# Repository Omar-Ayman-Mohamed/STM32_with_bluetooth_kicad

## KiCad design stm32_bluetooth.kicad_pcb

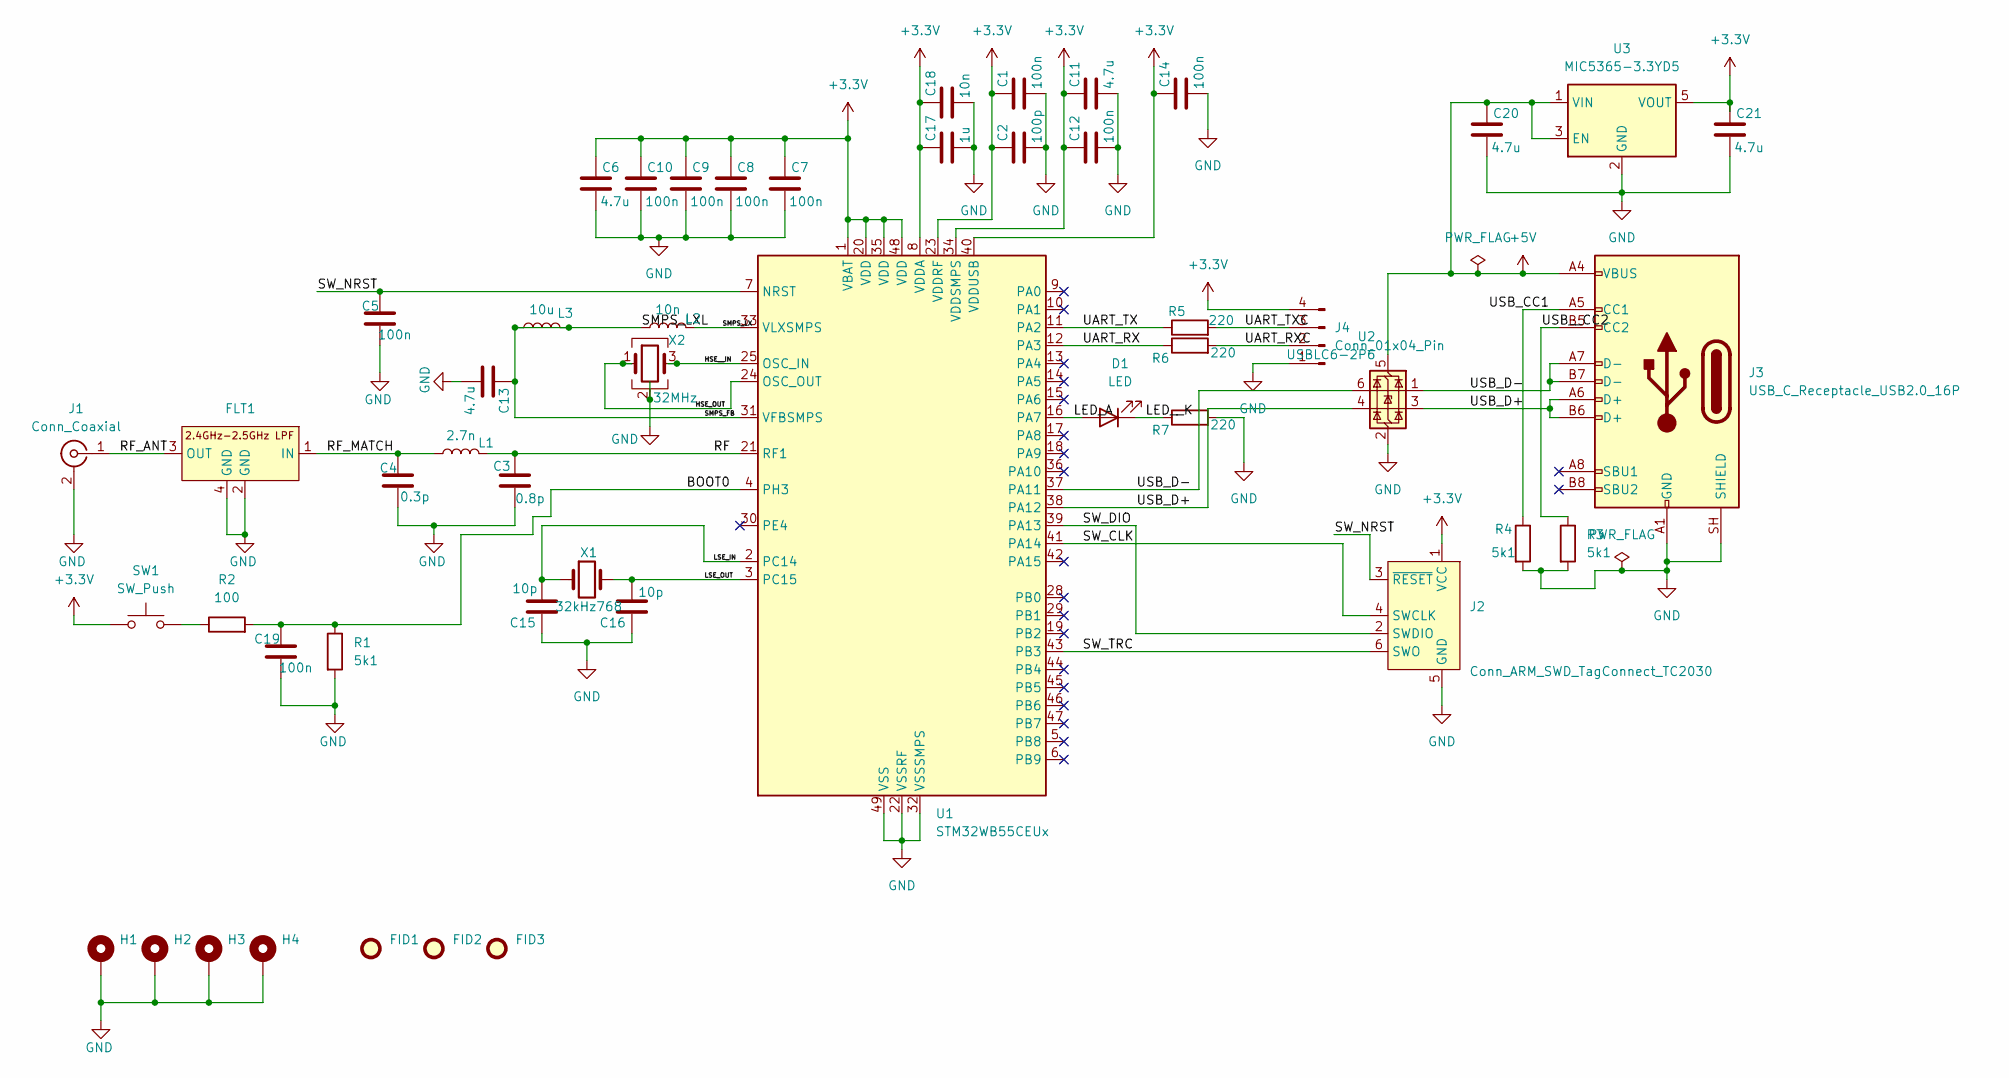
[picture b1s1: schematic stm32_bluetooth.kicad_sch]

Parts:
C1, C5, C7, C8, C9, C10, C12, C14, C19: 100n; C_0402_1005Metric
C2: 100p; C_0603_1608Metric
C3: 0.8p; C_0402_1005Metric
C4: 0.3p; C_0402_1005Metric
C6, C11, C13, C20, C21: 4.7u; C_0603_1608Metric
C15, C16: 10p; C_0402_1005Metric
C17: 1u; C_0603_1608Metric
C18: 10n; C_0402_1005Metric
D1: LED; LED_0402_1005Metric
FID1, FID2, FID3: Fiducial; Fiducial_1mm_Mask2mm
FLT1: DLF162500LT-5028A1
H1, H2, H3, H4: MountingHole_Pad; MountingHole_2.2mm_M2_Pad_Via
J1: Conn_Coaxial; U.FL_Hirose_U.FL-R-SMT-1_Vertical
J2: Conn_ARM_SWD_TagConnect_TC2030; Tag-Connect_TC2030-IDC-FP_2x03_P1.27mm_Vertical
J3: USB_C_Receptacle_USB2.0_16P; USB_C_Receptacle_GCT_USB4105-xx-A_16P_TopMnt_Horizontal
J4: Conn_01x04_Pin; Molex_PicoBlade_53048-0410_1x04_P1.25mm_Horizontal
L1: 2.7n; L_0402_1005Metric
L2: 10n; L_0402_1005Metric
L3: 10u; L_0805_2012Metric
R1, R3, R4: 5k1; R_0402_1005Metric
R2: 100; R_0402_1005Metric
R5, R6, R7: 220; R_0402_1005Metric
SW1: SW_Push; SW_SPST_CK_RS282G05A3
U1: STM32WB55CEUx; QFN-48-1EP_7x7mm_P0.5mm_EP5.6x5.6mm
U2: USBLC6-2P6; SOT-666
U3: MIC5365-3.3YD5; TSOT-23-5
X1: 32kHz768; Crystal_SMD_2012-2Pin_2.0x1.2mm
X2: 32MHz; Crystal_SMD_2016-4Pin_2.0x1.6mm

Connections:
+3.3V: C1.1, C2.1, C6.1, C7.1, C8.1, C9.1, C10.1, C11.1, C12.1, C14.1, C17.1, C18.1, C21.1, J2.1 (VCC), J4.4, SW1.1, U1.1 (VBAT), U1.8 (VDDA), U1.20 (VDD), U1.23 (VDDRF), U1.34 (VDDSMPS), U1.35 (VDD), U1.40 (VDDUSB), U1.48 (VDD), U3.5 (VOUT)
+5V: C20.1, J3.A4 (VBUS), J3.A9 (VBUS), J3.B4 (VBUS), J3.B9 (VBUS), U2.5 (VBUS), U3.1 (VIN), U3.3 (EN)
/BOOT0: C19.2, R1.1, R2.2, U1.4 (PH3)
/HSE_OUT: U1.24 (OSC_OUT), X2.1
/HSE__IN: U1.25 (OSC_IN), X2.3
/LED_A: D1.2 (A), U1.16 (PA7)
/LED__K: D1.1 (K), R7.1
/LSE_IN: C15.2, U1.2 (PC14), X1.1
/LSE_OUT: C16.2, U1.3 (PC15), X1.2
/RF: C3.2, L1.2, U1.21 (RF1)
/RF_ANT: FLT1.3 (OUT), J1.1 (In)
/RF_MATCH: C4.2, FLT1.1 (IN), L1.1
/SMPS_FB: C13.1, L2.1, L3.1, L3.2, U1.31 (VFBSMPS)
/SMPS_LX: L2.2, U1.33 (VLXSMPS)
/SW_CLK: J2.4 (SWCLK), U1.41 (PA14)
/SW_DIO: J2.2 (SWDIO), U1.39 (PA13)
/SW_NRST: C5.2, J2.3 (~RESET), U1.7 (NRST)
/SW_TRC: J2.6 (SWO), U1.43 (PB3)
/UART_RX: R6.1, U1.12 (PA3)
/UART_RXC: J4.2, R6.2
/UART_TX: R5.1, U1.11 (PA2)
/UART_TXC: J4.3, R5.2
/USB_CC1: J3.A5 (CC1), R4.1
/USB_D+: J3.A6 (D+), J3.B6 (D+), U1.38 (PA12), U2.3 (I/O2), U2.4 (I/O2)
/USB_D-: J3.A7 (D-), J3.B7 (D-), U1.37 (PA11), U2.1 (I/O1), U2.6 (I/O1)
/USB__CC2: J3.B5 (CC2), R3.1
GND: C1.2, C2.2, C3.1, C4.1, C5.1, C6.2, C7.2, C8.2, C9.2, C10.2, C11.2, C12.2, C13.2, C14.2, C15.1, C16.1, C17.2, C18.2, C19.1, C20.2, C21.2, FLT1.2 (GND), FLT1.4 (GND), H1.1 (1_1), H2.1 (1_1), H3.1 (1_1), H4.1 (1_1), J1.2 (Ext), J2.5 (GND), J3.A1 (GND), J3.A12 (GND), J3.B1 (GND), J3.B12 (GND), J3.SH (SHIELD), J4.1, R1.2, R3.2, R4.2, R7.2, U1.22 (VSSRF), U1.32 (VSSSMPS), U1.49 (VSS), U2.2 (GND), U3.2 (GND), X2.2 (G), X2.4 (G)
unnamed: R2.1, SW1.2

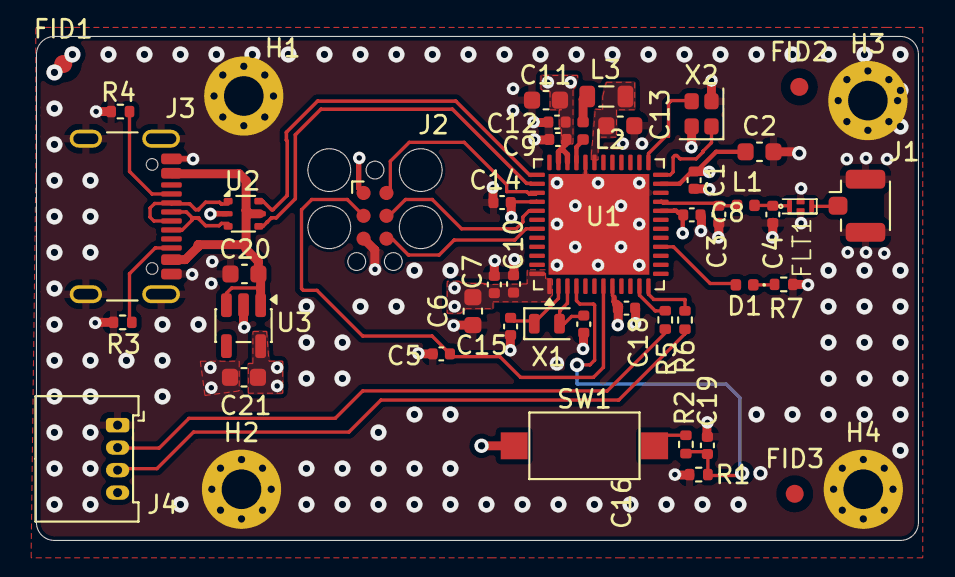
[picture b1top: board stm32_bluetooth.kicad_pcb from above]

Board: 4 copper layers, 49.0 x 28.0 mm, 49 parts (0 on the bottom side), 28 nets.
